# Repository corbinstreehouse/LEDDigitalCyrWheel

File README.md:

LEDDigitalCyrWheel
==================
This is my teensy 3.1 code for my LED cyr wheel v2 (by corbin dunn). I'm using individually addressable LEDs...so I called it "digital cyr wheel".

This project depends on a specific structure and some other projects. I use Mac OS; it may compile on other platforms, but I haven't tested it.

* Install Arduino; it must be installed in /Applications. I'm using 1.0.5

* Update submodules by doing this from the terminal:
 git submodule init
 git submodule update

* Optional: (TODO: upload my version): Libraries/OctoWS2811 -- much faster than NeoPixel, and originally my code could flip back and forth from using it and NeoPixel, but I haven't tested it in a while.

Once you have that setup, you should be able to open LEDDigitalCyrWheel.xcodeproj. To compile (see if that works first) select Build from the drop down menu and see if it compiles. Just select that target in the drop down in the toolbar and hit cmd-b to build.  If it doesn't, send me the errors and screen shots.

To upload, select Upload and hit cmd-b; this will launch the Teensy uploader, and you should see it uploading code. I usually just use Upload as it also builds.

The file to be aware of is Makefile. APP_LIBS_LIST are the Arduino built in libraries I use, for instance:
APP_LIBS_LIST = SPI Wire Wire/utility EEPROM

And you can tweak it if you use other libraries. Normally the Arduino IDE figures this out for you, but w/this Xcode project setup you have to do it yourself.

The other line to edit is USER_LIBS_LIST. It references the libraries in Ardunio/Libraries that I'm using. It says this currently:

USER_LIBS_LIST = Adafruit_NeoPixel SDFat SDFat/utility SD L3G LSM303

If I wanted to flip to

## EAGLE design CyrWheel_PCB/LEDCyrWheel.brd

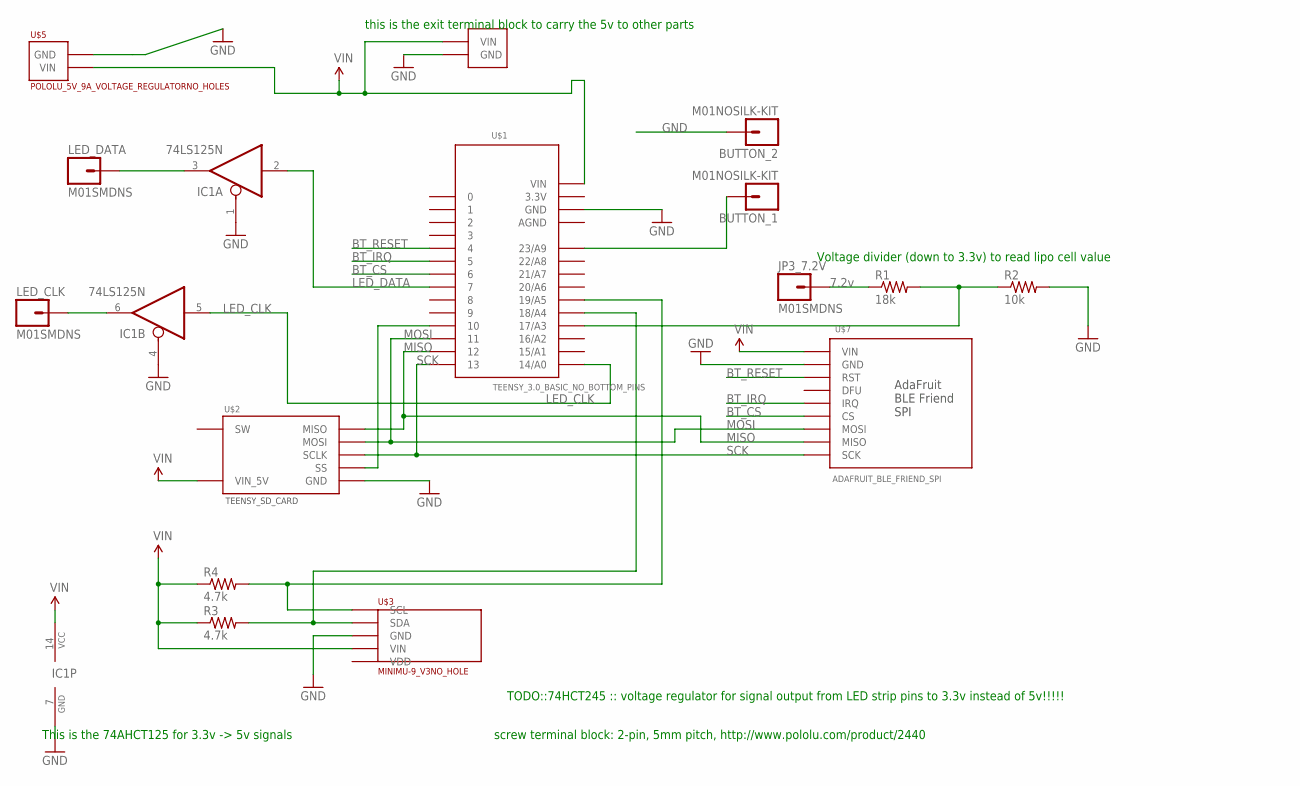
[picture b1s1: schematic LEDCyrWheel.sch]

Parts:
BUTTON_1, BUTTON_2: M01NOSILK-KIT; 1X01NS-KIT
IC1: 74LS125N; DIL14
JP3_7.2V: M01SMDNS; 1X01NS; VOLTAGE 7.2v
LED_CLK: M01SMDNS; 1X01NS
LED_DATA: M01SMDNS; 1X01NS
R1: 18k; AXIAL-0.4
R2: 10k; AXIAL-0.4
R3, R4: 4.7k; AXIAL-0.4
U$1: TEENSY_3.0_BASIC_NO_BOTTOM_PINS
U$2: TEENSY_SD_CARD
U$3: MINIMU-9_V3NO_HOLE; MINIMU-9_V3_NO_HOLE
U$5: POLOLU_5V_9A_VOLTAGE_REGULATORNO_HOLES; POLOLU_5V_9A_VOLTAGE_REGULATOR_NO_HOLES
U$6: VIN_GND_HOLE; VIN_HOLE
U$7: ADAFRUIT_BLE_FRIEND_SPI

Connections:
3.3V: U$1.3.3V
AGND: U$1.AGND
BT_CS: U$1.6, U$7.CS
BT_IRQ: U$1.5, U$7.IRQ
BT_RESET: U$1.4, U$7.RST
GND: BUTTON_2.1, IC1.1 (OE), IC1.4 (OE), IC1.7 (GND), R2.P$2 (2), U$1.GND, U$2.GND, U$3.GND, U$5.GND, U$5.GND2 (GND), U$5.GND3 (GND), U$6.GND, U$7.GND
LED_CLK: IC1.5 (I), U$1.14/A0
LED_DATA: IC1.2 (I), U$1.7
MISO: U$1.12, U$2.MISO, U$7.MISO
MOSI: U$1.11, U$2.MOSI, U$7.MOSI
unnamed: U$1.10, U$2.SS
unnamed: IC1.6 (O), LED_CLK.1
unnamed: BUTTON_1.1, U$1.23/A9
N_PIN17: R1.P$2 (2), R2.P$1 (1), U$1.17/A3
N_PIN_2_LED_STRIP: IC1.3 (O), LED_DATA.1
SCK: U$1.13, U$2.SCLK, U$7.SCK
SCL: R4.P$2 (2), U$1.19/A5, U$3.SCL
SDA: R3.P$2 (2), U$1.18/A4, U$3.SDA
VIN: IC1.14 (VCC), R3.P$1 (1), R4.P$1 (1), U$1.VIN, U$2.VIN (VIN_5V), U$3.VIN, U$5.VIN, U$5.VIN2 (VIN), U$5.VIN3 (VIN), U$6.VIN, U$7.VIN
VIN_7_2V: JP3_7.2V.1, R1.P$1 (1)

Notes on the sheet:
screw terminal block: 2-pin, 5mm pitch, http://www.pololu.com/product/2440
this is the exit terminal block to carry the 5v to other parts
Voltage divider (down to 3.3v) to read lipo cell value
TODO::74HCT245 :: voltage regulator for signal output from LED strip pins to 3.3v instead of 5v!!!!!
This is the 74AHCT125 for 3.3v -> 5v signals

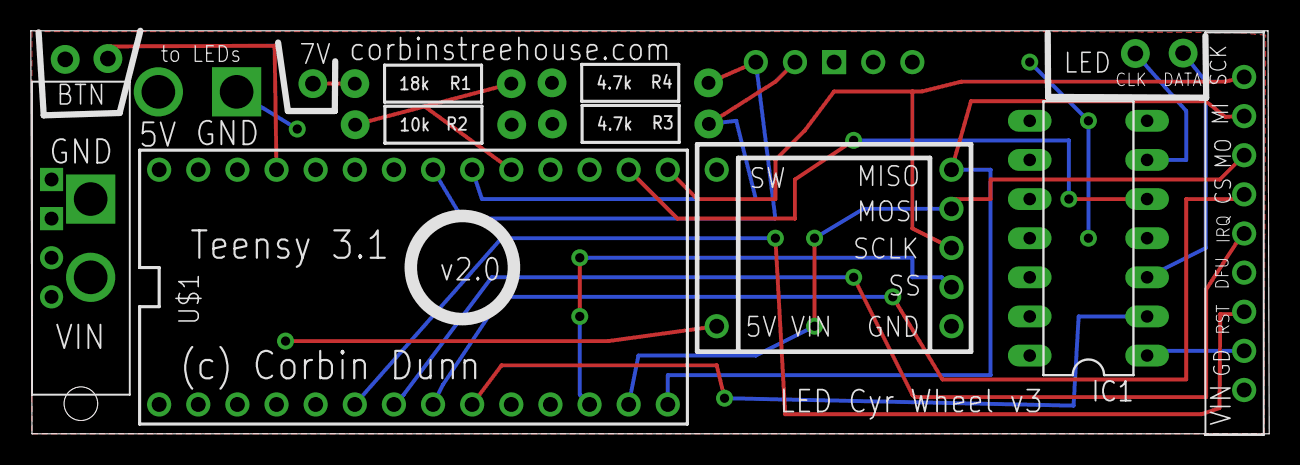
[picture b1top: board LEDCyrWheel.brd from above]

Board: 2 copper layers, 80.4 x 26.2 mm, 16 parts (1 on the bottom side), 18 nets.

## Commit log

2014-01-17 Initial checkin. It compiled a file for teensy 3.1!
2014-01-17 Upload now works.
2014-01-17 Mods
2014-01-17 Better code completion setup for teensy3
2014-01-17 Better git ignore
2014-01-17 ignore more stuff
2014-01-17 Code completion now works excellent!
2014-01-18 button and state
2014-01-20 use other stuff…
2014-02-03 using the sd library
2014-02-10 Work in progress
2014-02-10 Fix absolute paths
2014-02-11 Pattern sequence manager loading support.
2014-02-11 Last bit of work before refactorgin
2014-02-12 Massive refactoring to move LED patterns to a separate file. Not tested yet..but compiles.
2014-02-13 Abstraction fixes to i can compile in MacOS
2014-02-25 work in progress on sim
2014-02-25 More work for the simulator
2014-02-25 Rewrite of color wipe
2014-02-26 More pattern updates and add fade option
2014-02-26 Better color rainbow implementation. Fix compilation of hardware side.
2014-02-27 theater chase implementation
2014-02-27 Fade in/out
2014-02-28 Sequence name available now
2014-02-28 add back the delay on start to test
2014-02-28 better initialization for the default sequence
2014-02-28 Gobs smoother gradient work (took me a long time)
2014-03-01 debug/fix fading out and in. and loading SD card.
2014-03-01 Implement press and hold to switch sequences.
2014-03-01 fmod now found…use it
2014-03-01 LSM303 Accelerometer testing
2014-03-07 Fix event sending happening while processing hold
2014-03-07 implement voltage reading, etc
2014-03-07 fix brightness read
2014-03-29 gobs of work
2014-03-31 wave pattern
2014-03-31 bottom glow fixes..and wave multiple pattern
2014-04-01 bottom glow implementation...
2014-04-07 more patterns
2014-04-11 Before working on new image fading..
2014-04-12 linear fade pattern work.
2014-04-12 Entire fade added
2014-04-12 rework of buffer reading
2014-04-12 debugging sd card read problems
2014-04-12 Use the new SdFat library. actually works well
2014-04-19 Initial pass at an orientation class for accel/gyro readings.
2014-04-20 better initialization of the orientation class to a ctually work
2014-04-20 remove debug code
2014-04-20 Update the board platform tag to be 1.05 // 105 for arduino
2014-04-20 Better organization of flags to match what the Arduino IDE does
2014-04-20 trying to make this work better
2014-04-25 More orientation work.
2014-05-03 EEPROM reading of calibration data.
2014-05-11 Initial accell support
2014-05-11 remove #define ACCELEROMETER_SUPPORT 1 // not in the sim..
2014-05-30 some more work to try out the oct library; it conflict w/my pin uses...
2014-05-30 Move to sub projects.
2014-05-30 update to libraries
2014-05-30 References cleanup
2014-05-30 Add FastSPI
2014-05-31 Inclusion of FastLED
2014-06-01 New LED Patterns class / abstraction.
2014-06-01 Remove stuff not being used now.
2014-06-01 Fix typo
2014-06-04 Rework of the code to move LEDPatterns to a new shareable reusable class
2014-06-04 Update reference to other project
2014-06-04 fast LED update
2014-06-04 update fasted ref
2014-06-04 Move to LED Patterns project.
2014-06-04 Revert "Move to LED Patterns project."
    This reverts commit 415637c889b4a74561723b3203a5d02ef325d7d5.
2014-06-04 submodule updae
2014-06-04 Updaes
2014-06-04 ref update
2014-06-04 Updates to new patterns
2014-06-05 Other pixel patterns
2014-06-06 Remove old enum name
2014-06-07 Fire pattern, and up the sequence version..
2014-06-08 cross fade and flag pattern work
2014-06-08 Update to wavy patterns ref
2014-06-08 Update to sin wave pattern
2014-06-13 update to more patterns
2014-09-10 updated pattern use
2014-09-25 Gyro tweaks to not fail on init. Add more options to make the button not get hit.
2014-09-25 Updated sub project refs
2014-09-26 optional makefile mod to use LEDPatterns / FastLED and OctoWS2811 for testing
2014-09-26 Up the min voltage back up to 7.4; it wasn't hitting it, and just turning off!
2014-09-26 Updated pattern work/sizes
2014-09-28 bunch of updates
2014-09-28 Submodule update
2014-09-28 Move to my fork of FastLED on github
2014-09-30 I really am using pin 10. For reals, for SD card. This was probably the source of my problems….(or at least one part of many). Also, back to doing the battery ref check off…as it is clipped for now.
2014-10-11 Updated voltage reading
2014-10-11 Custom PCB files
2014-10-12 Initial Wifi support (server runs now)
2014-10-12 pattern ref up
2014-10-13 More server support
2014-10-14 define local path lengths incase I switch libraries.
2014-10-14 delay isn't needed
2014-10-14 Do spi init
2014-10-14 Teensyduino update to 1.20
2014-10-14 Updated Webduino ref
2014-10-14 Use the latest FastLED
2014-10-14 Updated LEDPatterns ref
2014-10-15 Back to using SD instead of SDFat
2014-10-15 Updated adafruit ref and del git submodule for SDFat
2014-10-20 Not really using SDFat, but I might.
2014-10-31 More web server commands implemented
2014-10-31 Wifi support abstracted better
2014-11-01 Updated use of state machine
2014-11-09 Tons of work to allow uploading of files via wifi
2014-11-09 Updated references
2015-11-12 updated checkout file. not sure what it is for
2015-11-12 Commented out code that didn't compile yet
2015-11-13 TeensyDuino should be defined as 120 not 117
2015-11-13 Compiles better with SPI_QUARTER_SPEED
2015-11-13 Don't use SD Fat; it doesn't compile
2015-11-14 Disable Wifi
2015-11-19 Make it compile with Arduino 1.6.6 and Teensy 1.2.6
2015-11-19 Bluetooth hacking
2015-11-19 Latest updates to FastLED
2015-11-19 Remove unused submodules
2015-11-24 Initial bluetooth work
2015-11-24 Updates blue
2015-11-30 Bluetooth WIP
2015-12-06 BMP support start
2015-12-06 abstraction to open multiple levels of files
2015-12-09 Initial bitmap support (need to move lazy bitmap to LED patterns)
2015-12-10 file not used
2015-12-10 moved to LED Patterns
2015-12-10 Rename some stuff
2015-12-10 Updated SD ref
2015-12-10 updated pattern rev
2015-12-10 Remove old SdFat ref
2015-12-12 Move to SD Fat
2015-12-12 Remove SD references
2015-12-12 remove filename copy need
2015-12-12 Ref my own hub for sdfat
2015-12-12 Update sdfat ref
2015-12-13 Simulator support etc
2015-12-13 Updated bitmap model
2015-12-13 Fix some crashes etc
2015-12-15 Updated bluetooth support
2015-12-17 More work
2015-12-22 Move to my ble
2015-12-22 Dot star hack use
2015-12-22 bluetooth speed testing.
2015-12-22 to neopxel for testing
2015-12-22 not used
2015-12-22 updated ref
2015-12-24 faster logic
2015-12-24 Copy of adafruit's code (not in a new repo..keeping it here
2015-12-25 Update FastLED Library use
2015-12-25 Updated arduino IDE use
2016-01-09 More compatability abstractions for the simulator
2016-01-17 Move the reset pin to 4 to be able to use pin 7
2016-01-17 Updates to using APA102 leds
2016-01-17 Fast LED hack implementation
2016-01-17 Updated hack for apa2
2016-01-18 LED speed notes
2016-01-18 cleanup
2016-01-18 duration shouldn't reset when it is 0; 0 means as fast as it can go
2016-01-22 Updated format for images by reference
2016-01-22 ref up
2016-01-22 Add in memory pattern loading from pattern editor
2016-01-23 ref up for LED Patterns
2016-01-24 Pattern updates
2016-01-24 Fixup duration
2016-01-26 better names
2016-01-29 More consistent struct size and alignment
2016-01-30 SdFat library update that uses proper transactions (on corbinstreehouse git hub)
2016-01-30 Ref the proper BT project that works
2016-01-30 Work around for flash of LEDs on start with APA102
2016-01-30 better intialial children size to avoid grow
2016-01-30 Turn bluetooth back on
2016-01-30 BT testing in progress
2016-01-30 spaces
2016-01-30 show boot progress
2016-02-01 octo not being used
2016-02-01 better eeprom management
2016-02-01 PCB design work
2016-02-01 Updated PCB design for new leds
2016-02-02 Updated PCB
2016-02-02 Updated BT LE support
2016-02-02 Pattern speed setting
2016-02-02 updated refs
2016-02-05 brightness fixes
2016-02-05 fixup code completion stuff by setting the compiler used in the project
2016-02-06 Allow playing programmed patterns
2016-02-06 dynamic image patterns
2016-02-06 dynamic support
2016-02-06 asdf
2016-02-07 better play/pause suport
2016-02-07 writing status WIP
2016-02-07 Sequence changed support for pushing to connected BT
2016-02-07 filename
2016-02-07 Long filename support for export
2016-02-07 bt debugging
2016-02-08 updated state
2016-02-08 less default patterns
2016-02-08 ble ref
2016-02-08 color and vel setting
2016-02-08 more options..
2016-02-09 remove stuff
2016-02-10 FPS char
2016-02-11 more bitmap options
2016-02-13 PCB fixes
2016-02-13 tweaks
2016-02-13 dynamic pattern playing
2016-02-13 slower BT refresh for POV
2016-02-13 File upload support
2016-02-14 #if ACCELEROMETER
2016-02-16 working on data streaming
2016-02-19 more abstract file sending mechanism
2016-02-25 New submodules
2016-02-25 orientation abstraction part 1
2016-03-05 orentation abstraction work
2016-03-05 refs
2016-03-13 Orientation abstraction
2016-04-01 my new LED strip length
2016-04-01 trying to fix SPI access to be faster.
2016-04-02 Format/comment tweaks
2016-04-08 BT init logic w/button down
2016-04-08 6mhz?
2016-04-11 Log the starting voltage
2016-04-11 Back to 8Mhz
2016-04-11 Maybe don't set DSE? I'm not sure what this is really for and if it is needed
2016-04-11 More debug logs
2016-04-11 new ref for patterns library
2016-04-14 look for figures too
2016-04-15 Some renames and timing rework
2016-04-15 Fix play
2016-04-15 Don't ignore voltage
2016-04-15 Debug OFF for now
2016-04-15 Timing rework for better direct offset assignment
2016-04-15 rwind
2016-04-15 fjx more jnk
2016-04-15 force show option
2016-04-20 Better default settings
2016-04-25 set the correction to LED strip
2016-05-07 slow down the speed (corruption) back to 7mhz, and remove color correction for now
2016-05-07 allow backing up easier
2018-04-25 Init only if the button is down for BT
2018-04-25 Update for libraries I guess
2018-12-08 Absolute paths for teensy location
2018-12-08 ignore ds store

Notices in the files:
parts and their libraries:
SparkFun-Connectors: Licensing: Creative Commons ShareAlike 4.0 International - https://creativecommons.org/licenses/by-sa/4.0
SparkFun: Licensing: CC v3.0 Share-Alike You are welcome to use this library for commercial purposes.
